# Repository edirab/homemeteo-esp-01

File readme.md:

## Проект домашней метеостанции на ESP-01 и Arduino

### О проекте:

Устройство раз в 2 секунды собирает данные о 
- температуре, 
- влажности воздуха, 
- влажности почвы и 
- относительной освещённости в двух точках 

Пакет по локальной сети через wifi отправляется MQTT-брокеру `mosquitto`, развёрнутом на `Raspberry Pi 3B`. Скрипт `mqtt_test.py`, который обработывает callback от брокера, накапливает данные, добавляет к ним временную метку и раз в 10 минут производит запись в базу данных.

Раз в сутки производится резервное копирование БД на флешку.
За день накапливается ~1,7 Mb

Собранные данные можно проанализировать и определить, например, 
- частоту полива цветка
- изменения температуры и влажности воздуха с временами года,
- изменение освещённости в течение дня и в течение года
- оценить продолжительность светового дня
( в том числе и во сколько автор ложится спать :) )

### Цели проекта: 

- освоить микроконтроллер `ESP 8266` в его проестейшей версии `ESP 01`
- познакомиться с протоколом MQTT
- реализовать надёжную двунаправленную связь по UART между микроконтроллерами на основе протокола с подтверждением
- углубить познания в отладке `cron`

### Состав репозитория

- Скетч `meteo.ino` для Arduino
- Скетч `esp_test.ino` для ESP-01
- Python-скрипт `mqtt_test.py`
- `bash`-скрипт для резервного копирования
- Проект KiCad 6.0: 
    + схема электическая принципиальная
    + примерная компоновка печатной платы
    + Bill of materials
- фото устройства
- описание для настройки автозапуска

### Развёртывание ПО

1. Установить зависимости
```shell
sudo apt update && sudo apt upgrade
pip3 install pysqlite3
pip3 install paho-mqtt
pip3 install python-telegram-bot --upgrade
pip3 install matplotlib
sudo apt install -y mosquitto mosquitto-clients
sudo systemctl enable mosquitto.service
```
2. Настроить `mqtt`-брокер
- отредактировать системный конфигурационный файл или
```shell
sudo nano /etc/mosquitto/mosquitto.conf
> listener 1883
> allow_anonymous true
```
- скопировать конфигурацию `my.conf`: `sudo cp <path_to_repo/my.conf> /etc/mosquitto/conf.d/`

3. `sudo reboot`
4. Проверка конфигурации брокера:
```shell
	mosquitto_sub -d -t hello/world
	mosquitto_pub -d -t hello/world -m "Hello from Terminal window 2!"
	mosquitto_sub -t home/#
```

### Настройка автозапуска приложения и резервного копирования

1. Устанавливаем права и запускаем вручную, чтобы создать первоначальный файл базы данных на флешке.
```shell
chmod +x *.sh
./mqtt_backup.sh
```
2. Редактируем таблицу `cron` от имени обычного пользователя. Явно добавляем переменные окружения, т.к. у `cron` они отличаются
```shell
crontab -e

SHELL=/bin/bash
HOME=/home/pi
PATH=/usr/local/sbin:/usr/local/bin:/usr/sbin:/usr/bin:/sbin:/bin:/usr/local/games:/usr/games	

@reboot 	 /usr/bin/python3 /home/pi/Documents/mqtt_test.py >> /home/pi/Documents/1.log &
# Каждый день в 15:50
50 15 * * *  /bin/bash  /home/pi/Documents/mqtt_backup.sh
```

3. Считываем заново таблицу
```shell
sudo service cron reload
```
4. Проверка автозапуска
```shell
sudo reboot
ps -ax | grep mqtt
```

#### Важно при настройке автозапуска по cron

1. Пути ко всем ресурсам как в `crontab`, так и внутри скрипта, лучше прописывать абсолютные
2. Ресурсы, к которым обраются скрипты, должны иметь соотв. права (БД и файл логов доступны для чтения/записи)
3. Использовать лучше таблицу для обычного пользователя, а не `root`, в противном случае придётся устанавливать все библиотеки и для root: `sudo pip3 install pysqlite3`
4. ! Формат записи: `# m h  dom mon dow   command` - сначала минуты!
5. Про переносе файла с windows на linux могут слететь окончания строк: `dos2unix <file>`
6. Для отладки пользоваться гайдом [отсюда](https://stackoverflow.com/questions/22743548/cronjob-not-running)

### Процесс разработки

- [x] Устанока и настройка `mqtt`-брокера на Raspberry Pi
- [x] Поиск/проверка скрипта на python для записи данных, полученных от брокера
- [x] Разработка тестового ПО для ESP-01 для отладки приёма данных по MQTT. Например, посылка миллисекунд с момента включения
- [x] Определиться что будем использовать: ардуино в связке в esp 01

- [x] Для этого нужно определиться с составом датчиков. Берём
  + DHT 22 (влажность/температура)
  + Влажность почвы (аналоговый вход)
  + Пара фоторезисторов (аналоговые входы)
	
- [x] Разработать формат UART-посылки. Принят такой вариант:
	`27.2 35.6 3 456 645\r\n`

- [x] Разработать метод для разбора посылки на стороне esp 01, пришедшей по последовательному интерфейсу
- [x] Протестировать взаимодействие устройств на макетной плате -> Минимальное жизнеспособное приложение!
- [x] Добавить 3 светодиода на ардуино: 
  + красный для сигнализации о потере mqtt-соединения,
  + жёлтый - сухая почва цветка
  + зелёный для сигнализации о потере wifi-соединения,

- [x] Начертить схему электрическую принципиальную
- [x] Сделать компоновку печатной платы
- [x] Собрать устройство на паечной макетной плате

- [x] Необходимо разработать более надёжный протокол управления, основанный на сообщениях 
с уникальными префиксами и подтверждениями 

- [x] Доработать скрипт на python. Нельзя вести запись на карту памяти каждые 2 секунды.
	Слишком большой износ. Сделать раз в 3-5 минут
- [x] Изменить схему базы данных для более компактного хранения данных

- [ ] Добавить обработку ЖЁЛТОГО светодиода, подобрать пороговое значение для влажности почвы
- [ ] Оформить проект красиво: сделать фото устройства, составить Bill of Materials, сохранить в pdf схему эл. принц.

- [x] Разобраться как настроить автозапуск скрипта при старте Raspbian

- [x] Добавить `bash`-скрипт для резервного копирования БД на флешку раз в сутки по `cron`
- [ ] Сделать бота для Телеграм, чтобы можно было получить доступ к данным из любой точки мира с телефона. Продумать функционал

- [ ] Как насчёт добавить какой-либо пользовательский интерфейс для задания новых
  + логина/пароля для wifi-сети,
  + ip-адреса mqtt-брокера

### Заметки

- [Задать пароль и пользователя для брокера mosquitto](http://www.steves-internet-guide.com/mqtt-username-password-example/)

- Откуда взят [mqtt_test.py](https://lindevs.com/save-mqtt-data-to-sqlite-database-using-python/)

### Настройка VS Code для работы с Arduino

- Установить плагин Arduino
- Прописать путь к библиотекам, устанавливаемым через менеджер: 
	`corsair2\\Documents\\Arduino\\libraries` в `arduino.json`
- Добавить параметр `"output": "build"` в `arduino.json`

- Логин пароль `esp/esp`

### Bootloader debug messages

При загрузке esp выкидывает в uart отладочную информацию о работе загрузчика.
Поделать с этим ничего нельзя, только проигнорировать.
Скорость baudrate 74800 bit/s

Для отключения подобного вывода необходимо GPIO 15 (MTDO) [притянуть к нулю](https://www.esp32.com/viewtopic.php?t=10597) ,
но на ESP-01 вывод не разведён

```
	Posting for someone who still needs help on this topic.
	[Note: I'm using IDFv4.4 dev]

	Step1: got to menuconfig -> component config -> esp system settings -> channel for console output
	Set to - Custom UART
	Come one level behind and you'll find new options: UART peripheral to use for console output
	Set this to UART1
	You may also change the pins for UART0/1 that you are using now, by writing them in "UART Tx in GPIO# " option,
	if you want to use UART0 pins (Tx-GPIO1 & Rx-GPIO3) for other purposes or simply change their respective pins to somewhere more convenient while designing a complex PCB.

	Now, save and quit menuconfig -> flash operation is always done through UART0 (GPIO 1&3) but monitoring can now be done through UART1
	However, on every reset (POWER_ON/SW_RESET/WDT_RESET, etc.) the UART0 pins will output bootloader logs even-though they are supposed to be printed through UART1. For this, I tried setting BOOTLOADER and LOGOUTPUT to NONE in menuconfig, but it only stopped printing the respective logs on UART1 (coz. we had set it that way).

	The real solution is to pulldown GPIO15 so that even those bootup logs at UART0 can be stopped and now you're free to use the GPIO 1&3 for I/O operations.
```

Единственный вариант - пропустить эти сообщения

### Отладка автозапуска

Способы настройки автозапуска
- rc.local
- init.d
- systemd
- cron
- .bashrc

##### 1. Скрипт dbg_cron.py

1.1 Для отладки запуска в cron по reboot создадим простой скрипт.
Просто выводим дату и время в файл

В crontab обычного пользователя добавим 
	@reboot /usr/bin/python3 /home/pi/Documents/dbg_cron.py

- Просмотр изменений файла:
	watch -n 1 tail -1 /tmp/dbg_cron.log
	sudo tail -n20 -f /var/log/mosquitto/mosquitto.log
	sudo cp /home/pi/Documents/mymqttclient.service /etc/systemd/system/

=====

cat /var/log/syslog | grep cron
cat /var/log/syslog | grep CRON
tail -f /var/log/syslog

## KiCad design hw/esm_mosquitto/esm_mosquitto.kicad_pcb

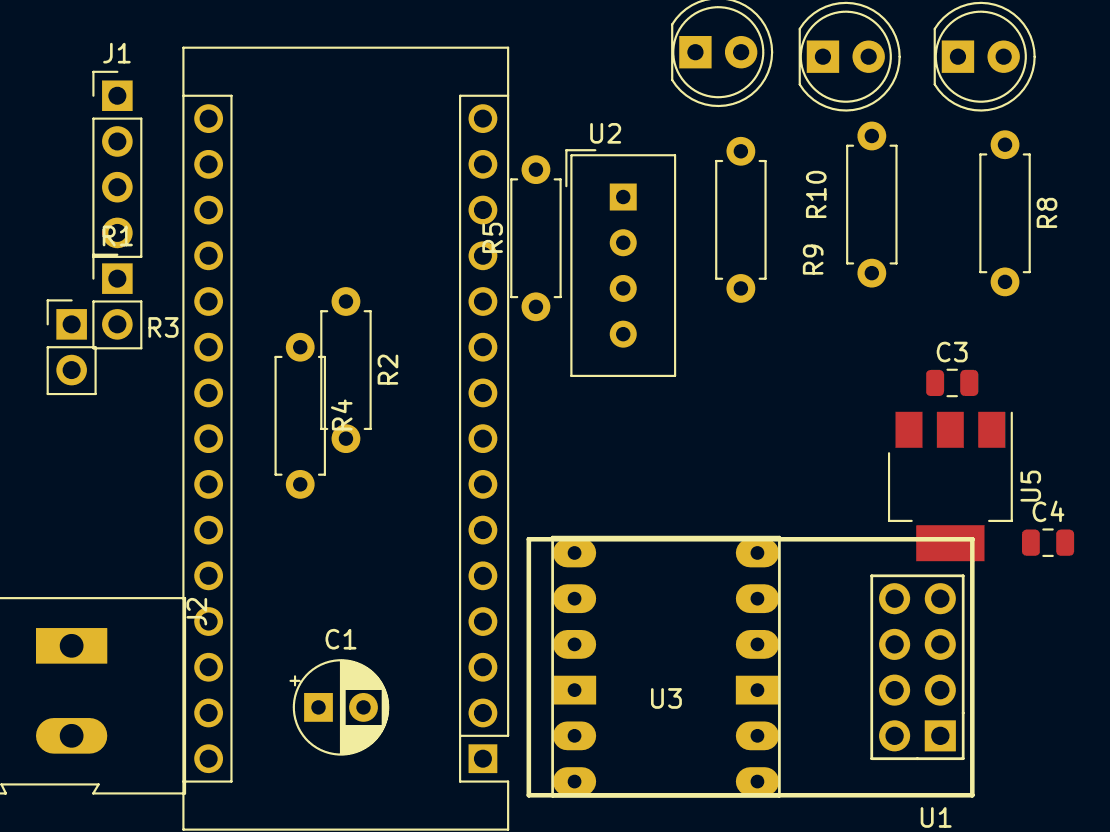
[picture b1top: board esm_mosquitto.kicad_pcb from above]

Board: 2 copper layers, 21 parts (0 on the bottom side), 17 nets, no tracks yet.

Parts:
A1: Arduino_Nano_v3.x; Arduino_Nano
C1: 220u; CP_Radial_D5.0mm_P2.50mm
C3: 10u; C_0805_2012Metric
C4: 22u; C_0805_2012Metric
D1: LED_G_wifi; LED_D5.0mm_Clear
D2: LED_Y_soil; LED_D5.0mm_Clear
D3: LED_R_mqtt; LED_D5.0mm_Clear
J1: Conn_01x04_Male_Soil_Sensor; PinHeader_1x04_P2.54mm_Vertical
J2: Barrel_Jack; TerminalBlock_Altech_AK300-2_P5.00mm
R1, R3: R_Photo; PinHeader_1x02_P2.54mm_Vertical
R2, R4: 1k; R_Axial_DIN0207_L6.3mm_D2.5mm_P7.62mm_Horizontal
R5: 10k; R_Axial_DIN0207_L6.3mm_D2.5mm_P7.62mm_Horizontal
R8, R9, R10: 470; R_Axial_DIN0207_L6.3mm_D2.5mm_P7.62mm_Horizontal
U1: ESP-01v090; ESP-01
U2: DHT11; Aosong_DHT11_5.5x12.0_P2.54mm
U3: BSS138_4ch; BSS138
U5: AMS1117-3.3; SOT-223-3_TabPin2

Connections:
+3V3: C4.1, U1.3 (CH_PD), U1.7 (VCC), U3.10 (LV), U5.2 (VO)
+5V: A1.27 (+5V), C1.1, C3.1, J1.1, J2.1, R1.1, R3.1, R5.1, U2.1 (VCC), U3.3 (HV), U5.3 (VI)
A0: A1.19 (A0), J1.4
A1: A1.20 (A1), R1.2, R2.1
A2: A1.21 (A2), R3.2, R4.1
DHT_OUT: A1.14 (D11), R5.2, U2.2 (IO)
GND: A1.4 (GND), A1.29 (GND), C1.2, C3.2, C4.2, D1.1 (K), D2.1 (K), D3.1 (K), J1.2, J2.2, R2.2, R4.2, U1.2 (GND), U2.4 (GND), U3.4 (GND), U3.9 (GND), U5.1 (GND)
unnamed: A1.9 (D6), R8.2
unnamed: A1.10 (D7), R9.2
unnamed: A1.11 (D8), R10.2
unnamed: D1.2 (A), R8.1
unnamed: D2.2 (A), R9.1
unnamed: D3.2 (A), R10.1
unnamed: U1.1 (UTXD), U3.12 (LV1)
unnamed: U1.8 (URXD), U3.11 (LV2)
RX: A1.2 (D0/RX), U3.1 (HV1)
TX: A1.1 (D1/TX), U3.2 (HV2)

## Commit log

2022-04-14 Начало проекта ESP-метеостанция
2022-04-14 Тестовый пример для обработки аналоговых данных
2022-04-14 Дополнен пример для ESP-01: написан разбор строки с данными, принятой по UART
2022-04-15 Создано минимальное жизнеспособное приложение. Код для ардуино объединил в себе все части. Исправлен баг порядка отправки данных в ESP-01
2022-04-18 Начало разработки схемы электрической принципиальной и компоновки печатной платы Не удаётся состыковать в обратную сторону ESP 01 Arduino для передачи информации о статусе беспроводного соединения
2022-04-18 Решена проблема с различными окончаниями строк, но ардуино всё равно не всегда принимает сообщения. Необходимо упростить протокол. 1 символ вместо целой строки
2022-04-18 Решена проблема с отбрасыванием мусора (отладочные сообщения загрузчика) от esp-01 на старте. Протокол отправика стстуса соединения теперь из одного байта. Это нехорошо, нужно сообщение подлиннее, чт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
2022-04-19 Компоновка завершена
2022-04-21 Собрано устройство на паечной макетной плате. Исправлены ошибки при монтаже, проверены напряжения питания. Изменена схема формирования напряжения 3.3 В, переназначены выводы для светодиодов и датчика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
2022-04-22 - Исправлена ошибка в подключении ESP 01: вывод EN подтянут к питанию - Допаяны последние провода - Устройство собрано в корпус
2022-04-25 - Исправлено подключение фоторезисторов: фоторезистор и резистор 1к поменяны местами - Допаян длинный провод для вилки датчика влажности почвы - Устройство проверено, работает как ожидается
2022-04-25 - Модифицирован протокол передачи статуса соединения: добавлен уникальный префикс сообщения и циклическая отправка до момента получения подтверждения - Проверена работа передачи статусов 3 и 4 (отклю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
2022-04-26 - В скрипте python запись в БД теперь происходит не раз в 2 секунды, а раз в 2 минуты. - Необходимо модифицировать схему БД, иначе слишком большой объём данных - Обнаружен баг в коде разбора строки н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
2022-04-26 - Изменена схема базы данных на более экономную - Соответственно, изменена логика периодической записи строк в БД в скрипте на python - Расширение теперь sqlite3
2022-04-26 - Начало написания ноутбука для анализа временных рядов - Исправлен баг с временной меткой
2022-04-26 - Настроен автозапуск python-скрипта по перезагрузке
2022-04-27 - Принято решение переработать формат посылки для mqtt-брокера, поскольку объединение данных из разных топиков вызывает сложности. Теперь все измерения пересылаются без изменений одной строкой. - Мод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
2022-04-27 - Переработан и значительно упрощён скрипт на python - Приложение в процессе тестирования
2022-04-28 - Настроен автозапуск по перезагрузке под cron
2022-04-28 - Настроен автозапуск резервного копирования
2022-04-28 - Реализован набор методов для анализа данных за произвольный период времени
2022-04-29 - Выборка данных каждые 10 секунд
2022-04-29 - Подготовлены изображения устройства
2022-04-29 - Добавлена схема электрическая принципиальная в pdf и Bill of materials
2022-04-30 - Начало создания телеграм-бота: минимальное жизнеспособное приложение - Readme: инструкция по установке зависимостей
2022-05-02 - Методы из jupyter ноутбука перенесены с файл stat.py. - Оформление графиков: размеры подписей и шрифтов - Написан метод для разбора параметров команды - Добавлен отладочный вывод в mqtt_test.py
2022-05-02 - Релизована команда /daily и её перегруженная версия /daily dd.mm - Обновлена база данных локально - Настроено сохранение изображений без обрезки подписей
2022-05-02 - Дописан обработчик команды help - Все команды зарегистрированы в BotFather и высплывают при нажатии на кнопку Меню - Пути к изображениям изменены на tmpfs
2022-05-03 - Настроен запуск бота на RPi - Исправлены пути в скрипте резервного копирования - Путь к БД перенесён в config.py - Построени графиков с помощью pandas в ноутбуке
